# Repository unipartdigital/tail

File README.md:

# Tail
Tail - an indoor position system using UWB radio

# Description

Tail consists of tags, anchors and a server.

A tag is a battery-powered device which occasionally transmits a packet on UWB radio.

An anchor is an externally-powered device in a fixed location which acts as a bridge between UWB radio and the network on which the server resides.

The server sends and receives packets via the anchors, and is able to compute the location of each tag using multilateration.

A simpler mode of operation has also been developed whereby an anchor and a tag perform two-way communications to establish a distance between a tag and a single anchor.

# Status

Tail has been developed to a functional demo in a constrained test environment. It requires further development before it can be used in a production environment.

Unipart Digital is not currently developing this project past this stage.

# Video

Unipart Digital produced a video showing how the system works, and demonstrating it in action. The video is available here:

https://unipart.digital/images/projects/tail/tail-commercial.mp4

# Repositories

## tail
This repository is the monorepo that was used for the duration of the development project, so contains everything related to the tags - firmware, hardware, CAD etc,
various works on the anchor software as well as a number of scripts, utilities and other bits and pieces.

## dw1000
https://github.com/unipartdigital/dw1000

This contains hardware and drivers for a DW1000 interface card for a Raspberry Pi

## utrack-tail
https://github.com/unipartdigital/utrack-tail

This repository contains the standalone anchor code required for the two-way communications mode.

## tail-server
https://github.com/unipartdigital/tail-server

This repository contains the latest attempt at developing a multilaterating server for the one way ranging mode.

## tail-anchor-hardware
https://github.com/unipartdigital/tail-anchor-hardware

This repository contains the hardware for a standalone anchor

## tail-anchor-firmware
https://github.com/unipartdigital/tail-anchor-firmware

This repository contains the (as yet barely started) firmware for a standalone anchor

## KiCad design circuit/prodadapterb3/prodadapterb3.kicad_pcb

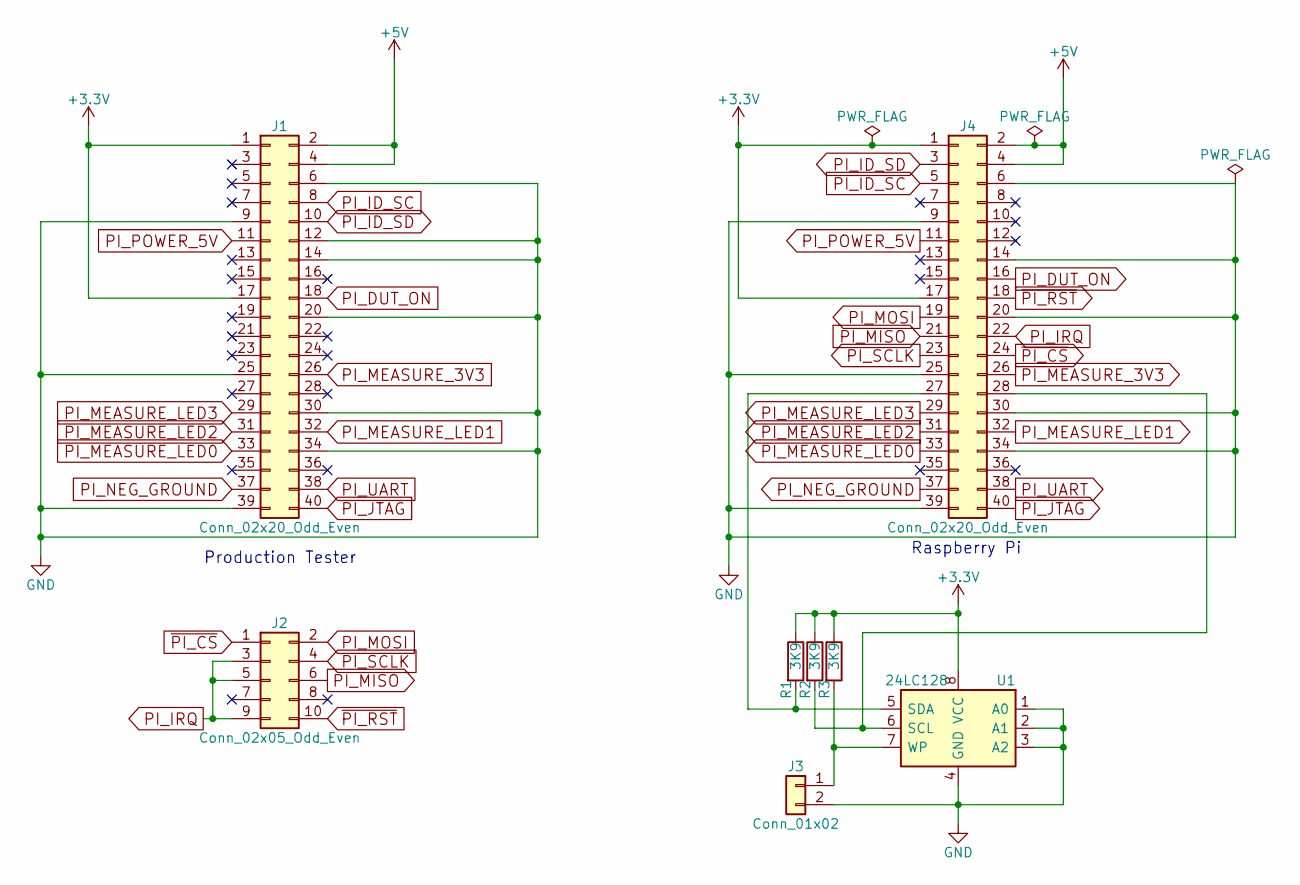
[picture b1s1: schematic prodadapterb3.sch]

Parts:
J1, J4: Conn_02x20_Odd_Even; Pin_Header_Angled_2x20_Pitch2.54mm; MPN 09 18 540 6903
J2: Conn_02x05_Odd_Even; Pin_Header_Angled_2x05_Pitch1.27mm; MPN FTSH-105-01-L-D-RA-K
J3: Conn_01x02; Pin_Header_Straight_1x02_Pitch2.54mm; MPN 2211S-02G
R1, R2, R3: 3K9; R_Axial_DIN0204_L3.6mm_D1.6mm_P5.08mm_Horizontal; MPN MF12 3K9
U1: 24LC128; DIP-8_W7.62mm; MPN 24LC128-I/P

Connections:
+3V3: J1.1, J1.17, J4.1, J4.17, R1.1, R2.1, R3.1, U1.8 (VCC)
+5V: J1.2, J1.4, J4.2, J4.4
GND: J1.6, J1.9, J1.12, J1.14, J1.20, J1.25, J1.30, J1.34, J1.39, J3.2, J4.6, J4.9, J4.14, J4.20, J4.25, J4.30, J4.34, J4.39, U1.1 (A0), U1.2 (A1), U1.3 (A2), U1.4 (GND)
unnamed: J3.1, R3.2, U1.7 (WP)
unnamed: J4.27, R1.2, U1.5 (SDA)
unnamed: J4.28, R2.2, U1.6 (SCL)
PI_DUT_ON: J1.18, J4.16
PI_ID_SC: J1.8, J4.5
PI_ID_SD: J1.10, J4.3
PI_IRQ: J2.3, J2.5, J2.9, J4.22
PI_JTAG: J1.40, J4.40
PI_MEASURE_3V3: J1.26, J4.26
PI_MEASURE_LED0: J1.33, J4.33
PI_MEASURE_LED1: J1.32, J4.32
PI_MEASURE_LED2: J1.31, J4.31
PI_MEASURE_LED3: J1.29, J4.29
PI_MISO: J2.6, J4.21
PI_MOSI: J2.2, J4.19
PI_NEG_GROUND: J1.37, J4.37
PI_POWER_5V: J1.11, J4.11
PI_SCLK: J2.4, J4.23
PI_UART: J1.38, J4.38
~PI_CS: J2.1, J4.24
~PI_RST: J2.10, J4.18

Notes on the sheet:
Raspberry Pi
Production Tester

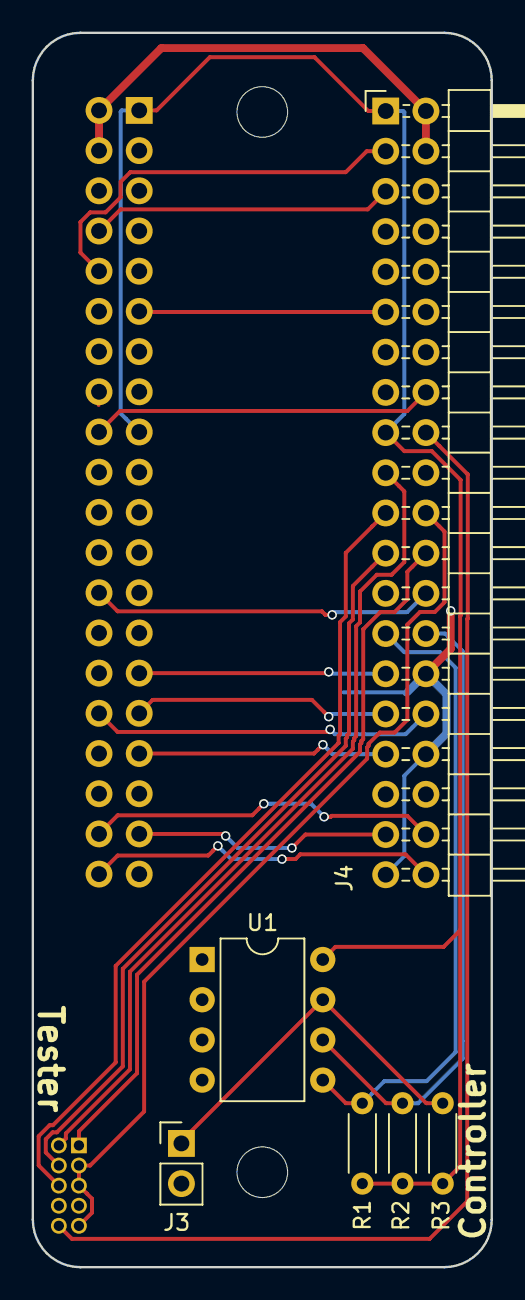
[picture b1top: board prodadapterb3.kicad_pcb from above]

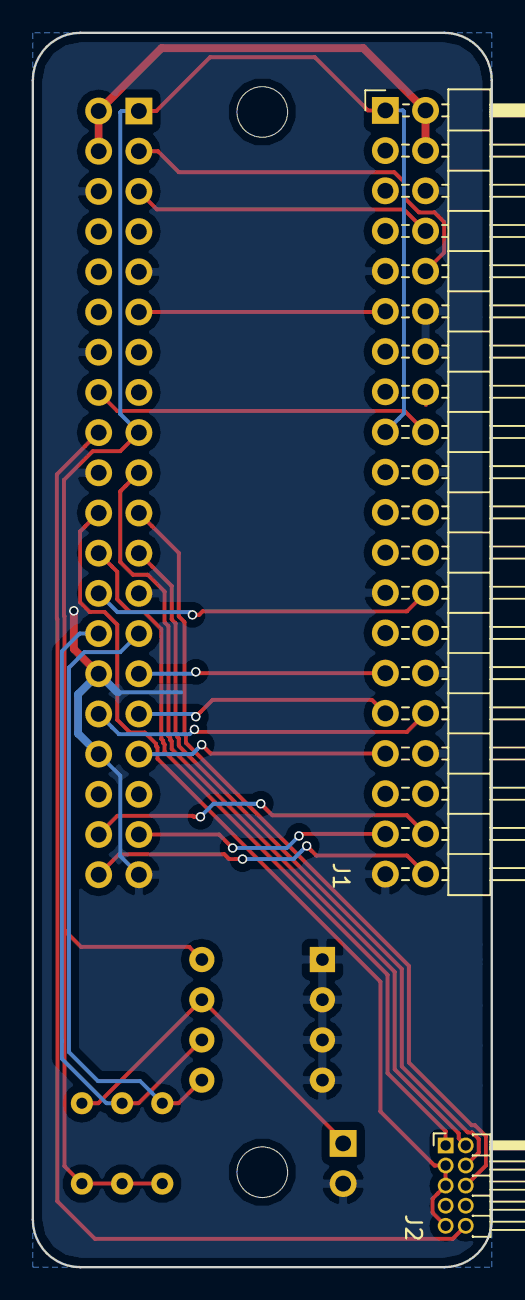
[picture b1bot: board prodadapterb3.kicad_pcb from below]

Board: 2 copper layers, 29.0 x 78.0 mm, 8 parts (2 on the bottom side), 24 nets.

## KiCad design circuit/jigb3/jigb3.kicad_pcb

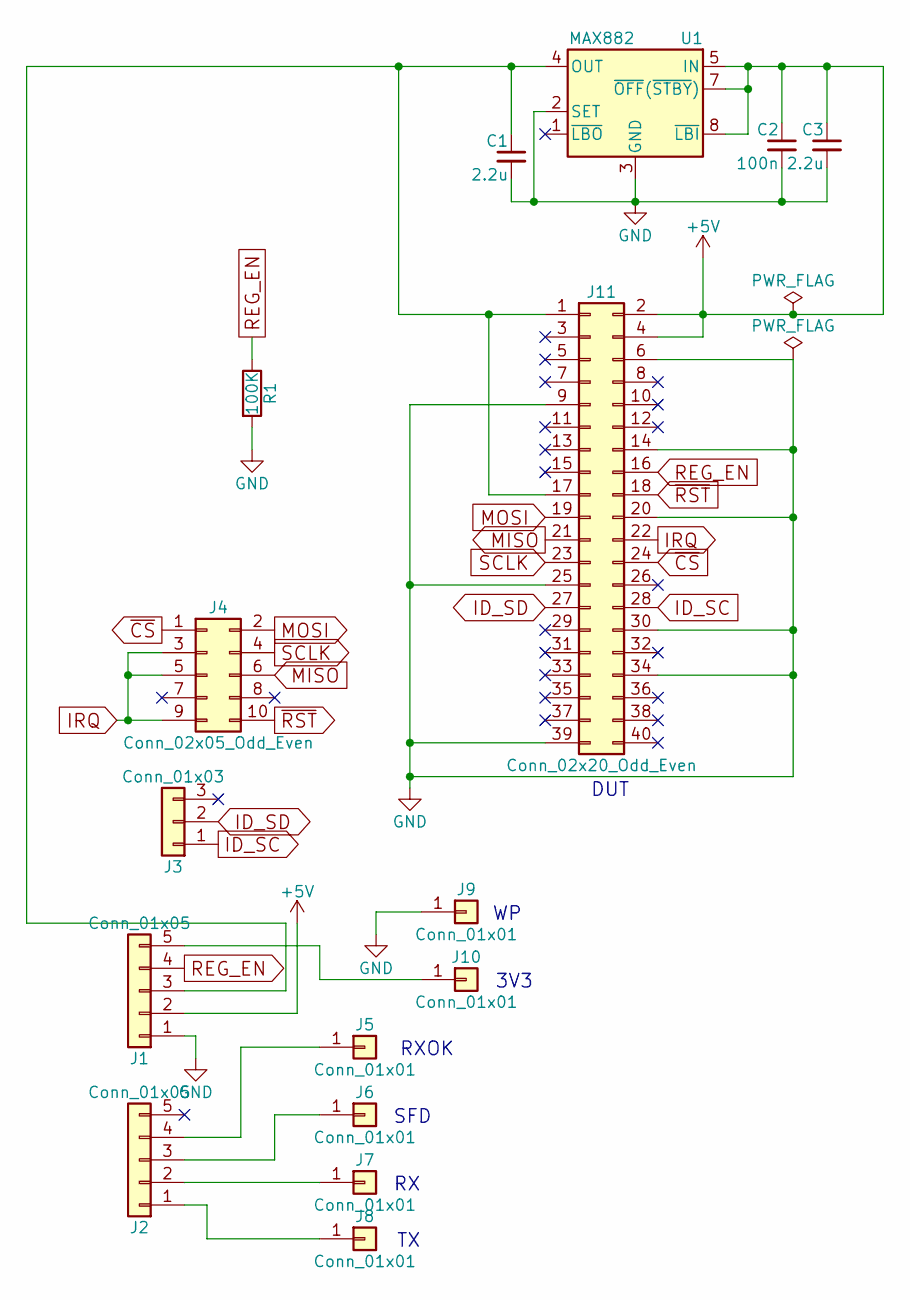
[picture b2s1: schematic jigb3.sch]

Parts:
C1, C3: 2.2u; CP_Radial_D5.0mm_P2.00mm; MPN MCRH100V225M5X11
C2: 100n; C_Disc_D5.0mm_W2.5mm_P5.00mm; MPN K104K15X7RF53H5
J1, J2: Conn_01x05; Pin_Header_Angled_1x05_Pitch2.54mm; MPN 61300511021
J3: Conn_01x03; Pin_Header_Angled_1x03_Pitch2.54mm; MPN 61300311021
J4: Conn_02x05_Odd_Even; Pin_Header_Angled_2x05_Pitch1.27mm; MPN FTSH-105-01-L-D-RA-K
J5, J6, J7, J8, J9, J10: Conn_01x01; P70-2200045; MPN P70-2200045
J11: Conn_02x20_Odd_Even; Pin_Header_Straight_2x20_Pitch2.54mm; MPN 2213S-40G
R1: 100K; R_Axial_DIN0204_L3.6mm_D1.6mm_P5.08mm_Horizontal; MPN MF12 100K
U1: MAX882; DIP-8_W7.62mm; MPN MAX882CPA+

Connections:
+5V: C2.1, C3.1, J1.2, J11.2, J11.4, U1.5 (IN), U1.7 (~OFF~(~STBY~)), U1.8 (~LBI)
GND: C1.2, C2.2, C3.2, J1.1, J9.1, J11.6, J11.9, J11.14, J11.20, J11.25, J11.30, J11.34, J11.39, R1.2, U1.2 (SET), U1.3 (GND), U1.6 (GND)
ID_SC: J3.1, J11.28
ID_SD: J3.2, J11.27
IRQ: J4.3, J4.5, J4.9, J11.22
MISO: J4.6, J11.21
MOSI: J4.2, J11.19
unnamed: C1.1, J1.3, J11.1, J11.17, U1.4 (OUT)
unnamed: J1.5, J10.1
unnamed: J2.1, J8.1
unnamed: J2.2, J7.1
unnamed: J2.3, J6.1
unnamed: J2.4, J5.1
REG_EN: J1.4, J11.16, R1.1
SCLK: J4.4, J11.23
~CS: J4.1, J11.24
~RST: J4.10, J11.18

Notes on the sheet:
DUT
3V3
RXOK
SFD

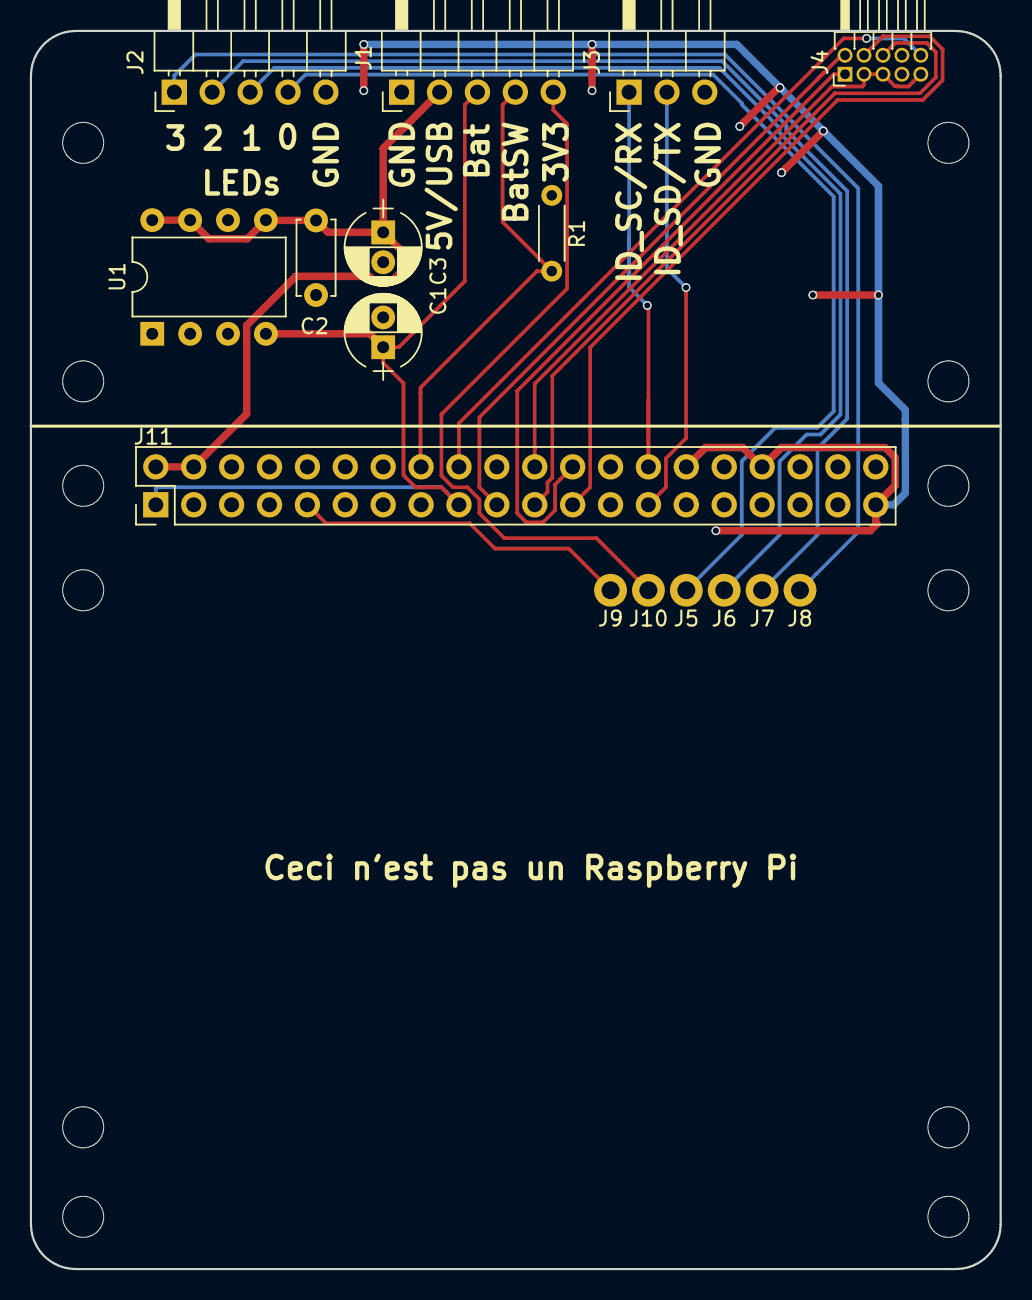
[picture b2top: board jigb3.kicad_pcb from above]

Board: 2 copper layers, 65.0 x 83.0 mm, 16 parts (0 on the bottom side), 17 nets.

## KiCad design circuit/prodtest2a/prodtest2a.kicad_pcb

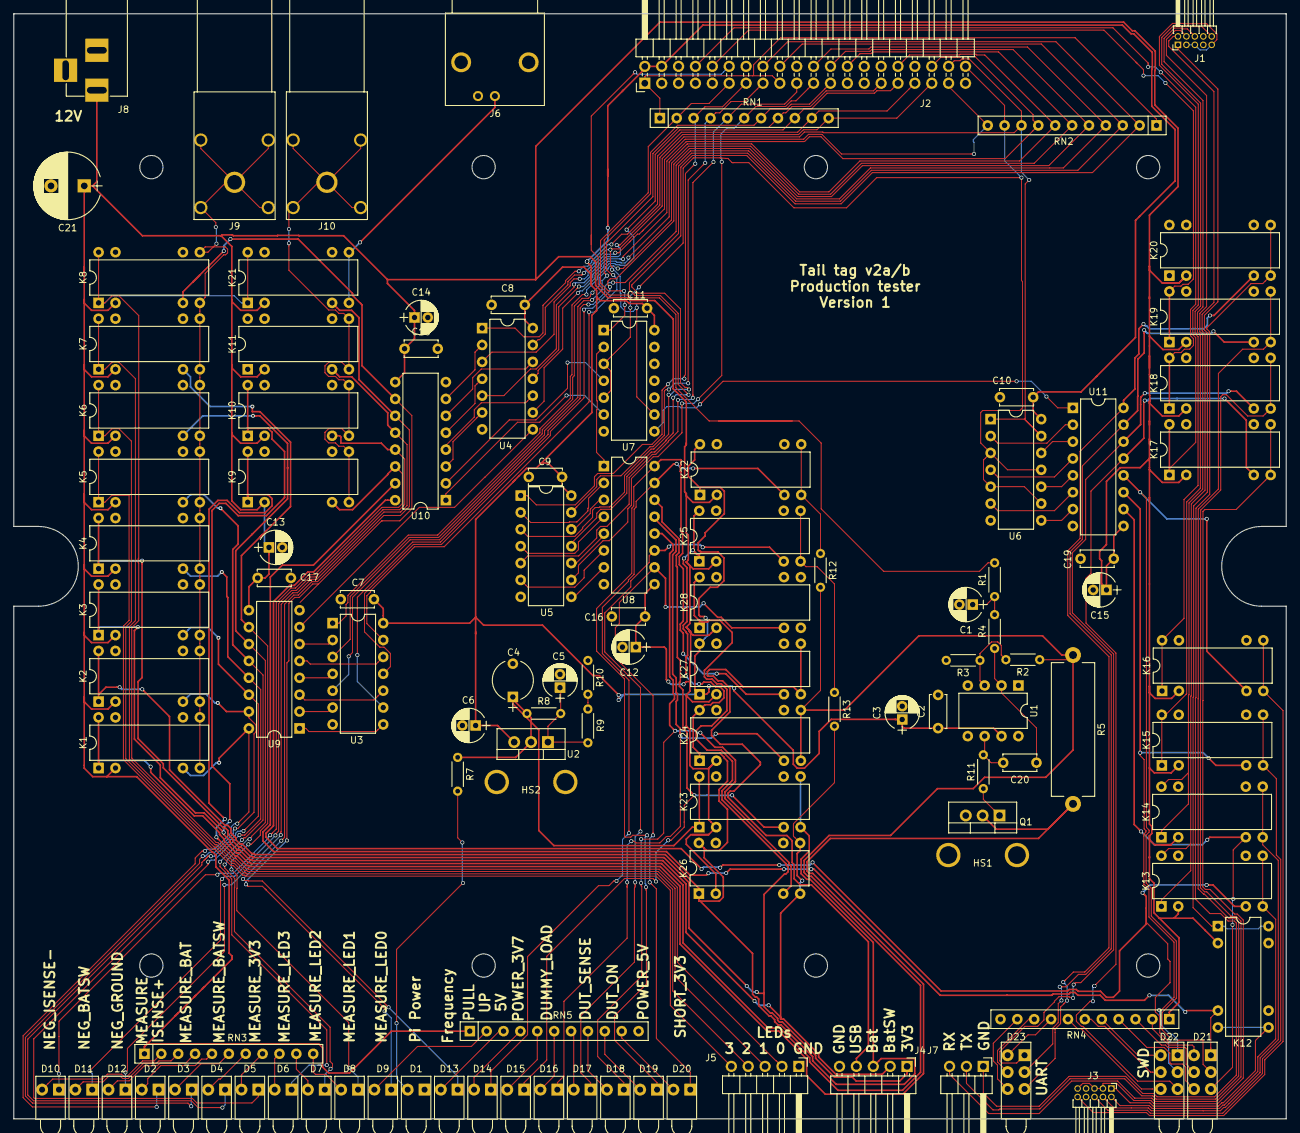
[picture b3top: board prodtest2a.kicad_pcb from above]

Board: 2 copper layers, 191.5 x 166.3 mm, 113 parts (0 on the bottom side), 150 nets.

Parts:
C1, C3, C5, C6, C12, C13, C14, C15: 10u; CP_Radial_D5.0mm_P2.00mm
C2, C7, C8, C9, C10, C11, C16, C17, C18, C19, C20: 100n; C_Disc_D5.0mm_W2.5mm_P5.00mm
C4: 22u; CP_Radial_Tantal_D6.0mm_P5.00mm
C21: 1000u; CP_Radial_D10.0mm_P5.00mm
D1: GREEN; LED_D3.0mm_Horizontal_Housing_Z5.0mm
D2, D3, D4, D5, D6, D7, D8, D9, D10, D11, D12, D13, D14, D15, D16, D17, D18, D19, D20: RED; LED_D3.0mm_Horizontal_Housing_Z5.0mm
D21, D22, D23: Green; LED_D3.0mm_Horizontal_Housing_Triple
HS1, HS2: Heatsink; Heatsink_Aavid_581002B02500G
J1, J3: Conn_02x05_Odd_Even; Pin_Header_Angled_2x05_Pitch1.27mm
J2: Conn_02x20_Odd_Even; Pin_Header_Angled_2x20_Pitch2.54mm
J4, J5: Conn_01x05; Pin_Header_Angled_1x05_Pitch2.54mm
J6: Conn_Coaxial; BNC_Elbow_Socket_TE_1-1337543-0
J7: Conn_01x03; Pin_Header_Angled_1x03_Pitch2.54mm
J8: Barrel_Jack; BARREL_JACK
J9: Banana Red; Staubli_4mm_Angled_Socket
J10: Banana Black; Staubli_4mm_Angled_Socket
K1, K2, K3, K4, K5, K6, K7, K8, K9, K10, K11, K12, K13, K14, K15, K16, K17, K18, K19, K20, K21, K22, K23, K24, K25, K26, K27, K28: HE721A; DIP-14_8_W7.62mm
Q1: IPP034N03L; TO-220-3_Vertical
R1: 4k7; R_Axial_DIN0204_L3.6mm_D1.6mm_P5.08mm_Horizontal
R2, R3: 100k; R_Axial_DIN0204_L3.6mm_D1.6mm_P5.08mm_Horizontal
R4, R13: 10k; R_Axial_DIN0204_L3.6mm_D1.6mm_P5.08mm_Horizontal
R5: 0R2; R_Axial_Power_L20.0mm_W6.4mm_P22.40mm
R7, R8, R9, R10: 100; R_Axial_DIN0204_L3.6mm_D1.6mm_P5.08mm_Horizontal
R11, R12: 1k; R_Axial_DIN0204_L3.6mm_D1.6mm_P5.08mm_Horizontal
RN1, RN2: 10k; R_Array_SIP11
RN3, RN4, RN5: 1k; R_Array_SIP11
U1: MCP601-xP; DIP-8_W7.62mm
U2: LM1084-ADJ; TO-220-3_Vertical
U3, U4, U5, U6, U7: 74HCT04; DIP-14_W7.62mm
U8, U9, U10, U11: ULN2003A; DIP-16_W7.62mm

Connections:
3V3: J4.1, K4.1, K4.14, K28.1, K28.14
3V7: C4.1, K23.1, K23.14, R7.1, R8.1, U2.2
+5V: C2.1, C3.1, C6.1, C7.1, C8.1, C9.1, C10.1, C11.1, J2.2, J2.4, K22.1, K22.14, K27.1, K27.14, U1.7, U2.3, U3.14, U4.14, U5.14, U6.14, U7.14
+12V: C12.1, C13.1, C14.1, C15.1, C16.1, C17.1, C18.1, C19.1, C21.1, J8.1, K1.2, K2.2, K3.2, K4.2, K5.2, K6.2, K7.2, K8.2, K9.2, K10.2, K11.2, K12.2, K13.2, K14.2, K15.2, K16.2, K17.2, K18.2, K19.2, K20.2, K21.2, K22.2, K23.2, K24.2, K25.2, K26.2, K27.2, K28.2, RN3.1, RN4.1, RN5.1, U8.9, U9.9, U10.9, U11.9
BATSIM: K1.1, K1.14, K24.7, K24.8, R2.1, R5.1, R12.2
Bat: J4.3, K2.1, K2.14, K23.7, K23.8, K24.1, K24.14, K25.1, K25.14, K26.1, K26.14
BatSW: J4.2, K3.1, K3.14, K10.1, K10.14, K26.7, K26.8, R13.2
C_DUMMY_LOAD: D16.1, K24.6, U8.13
C_DUT_ON: D18.1, K26.6, U8.12
C_DUT_SENSE: D17.1, K25.6, U8.11
C_FREQUENCY: D13.1, K21.6, U10.11
C_MEASURE_3V3: D5.1, K4.6, U9.13
C_MEASURE_BAT: D3.1, K2.6, U9.15
C_MEASURE_BATSW: D4.1, K3.6, U9.14
C_MEASURE_ISENSE+: D2.1, K1.6, U9.16
C_MEASURE_LED0: D9.1, K8.6, U10.10
C_MEASURE_LED1: D8.1, K7.6, U9.10
C_MEASURE_LED2: D7.1, K6.6, U9.11
C_MEASURE_LED3: D6.1, K5.6, U9.12
C_NEG_BATSW: D11.1, K10.6, U10.13
C_NEG_GROUND: D12.1, K11.6, U10.12
C_NEG_ISENSE-: D10.1, K9.6, U10.14
C_POWER_3V7: D15.1, K23.6, U8.14
C_POWER_5V: D19.1, K27.6, U8.16
C_PULLUP_5V: D14.1, K22.6, U8.15
C_SHORT_3V3: D20.1, K28.6, U8.10
C_SWCLK: D21.3, K14.6, U11.10
C_SWDIO: D21.2, K13.6, U10.16
C_SWD_GND: D22.3, K17.6, U11.13
C_SWD_RESET: D22.2, K16.6, U11.12
C_SWD_VCC: D21.1, K12.6, U10.15
C_SWO: D22.1, K15.6, U11.11
C_UART_GND: D23.3, K20.6, U11.16
C_UART_RX: D23.1, K18.6, U11.14
C_UART_TX: D23.2, K19.6, U11.15
FREQUENCY: J6.1, K21.7, K21.8
GND: C1.2, C2.2, C3.2, C4.2, C5.2, C6.2, C7.2, C8.2, C9.2, C10.2, C11.2, C12.2, C13.2, C14.2, C15.2, C16.2, C17.2, C18.2, C19.2, C21.2, D1.1, J2.6, J2.9, J2.14, J2.20, J2.25, J2.30, J2.34, J2.39, J4.5, J6.2, J8.2, J8.3, K11.1, K11.14, K20.1, K20.14, K28.7, K28.8, Q1.3, R3.2, R10.2, U1.4, U3.7, U4.7, U5.7, U6.7, U7.7, U7.11, U7.13, U8.8, U9.8, U10.8, U11.8
ISENSE-: K9.1, K9.14, Q1.2, R5.2
LED0: J5.2, K8.1, K8.14, K21.1, K21.14
LED1: J5.3, K7.1, K7.14
LED2: J5.4, K6.1, K6.14
LED3: J5.5, K5.1, K5.14
METER+: J9.1, K1.7, K1.8, K2.7, K2.8, K3.7, K3.8, K4.7, K4.8, K5.7, K5.8, K6.7, K6.8, K7.7, K7.8, K8.7, K8.8
METER-: J10.1, K9.7, K9.8, K10.7, K10.8, K11.7, K11.8
unnamed: C1.1, R1.1, R4.2
unnamed: C5.1, R8.2, R9.1, U2.1
unnamed: C20.1, R4.1, U1.2
unnamed: C20.2, R11.2, U1.6
unnamed: D1.2, R7.2
unnamed: D2.2, RN3.5
unnamed: D3.2, RN3.6
unnamed: D4.2, RN3.7
unnamed: D5.2, RN3.8
unnamed: D6.2, RN3.9
unnamed: D7.2, RN3.10
unnamed: D8.2, RN3.11
unnamed: D9.2, RN5.2
unnamed: D10.2, RN3.2
unnamed: D11.2, RN3.3
unnamed: D12.2, RN3.4
unnamed: D13.2, RN5.3
unnamed: D14.2, RN5.4
unnamed: D15.2, RN5.5
unnamed: D16.2, RN5.6
unnamed: D17.2, RN5.7
unnamed: D18.2, RN5.8
unnamed: D19.2, RN5.9
unnamed: D20.2, RN5.10
unnamed: D21.4, RN4.4
unnamed: D21.5, RN4.3
unnamed: D21.6, RN4.2
unnamed: D22.4, RN4.7
unnamed: D22.5, RN4.6
unnamed: D22.6, RN4.5
unnamed: D23.4, RN4.10
unnamed: D23.5, RN4.9
unnamed: D23.6, RN4.8
unnamed: J2.1, J2.17, RN1.1, RN2.1
unnamed: K22.7, K22.8, R12.1
unnamed: K25.7, K25.8, R13.1
unnamed: Q1.1, R11.1
unnamed: R2.2, R3.1, U1.3
unnamed: R9.2, R10.1
unnamed: U3.2, U9.6
unnamed: U3.4, U9.4
unnamed: U3.6, U9.2
unnamed: U3.8, U9.1
unnamed: U3.10, U9.3
unnamed: U3.12, U9.5
unnamed: U4.8, U9.7
unnamed: U5.2, U8.2
unnamed: U5.4, U8.4
unnamed: U5.6, U8.6
unnamed: U5.8, U8.7
unnamed: U5.10, U8.5
unnamed: U5.12, U8.3
unnamed: U7.2, U8.1
unnamed: U7.6, U10.1
unnamed: U7.4, U10.2
unnamed: U4.6, U10.3
unnamed: U4.10, U10.4
unnamed: U4.4, U10.5
unnamed: U4.12, U10.6
unnamed: U4.2, U10.7
unnamed: U7.8, U11.1
unnamed: U6.2, U11.2
unnamed: U6.12, U11.3
unnamed: U6.4, U11.4
unnamed: U6.10, U11.5
unnamed: U6.6, U11.6
unnamed: U6.8, U11.7
PI_DUMMY_LOAD: J2.16, RN2.2, U5.3
PI_DUT_ON: J2.18, RN2.3, U5.11
PI_DUT_SENSE: J2.19, RN1.5, U5.5
PI_JTAG: J2.40, RN2.10, U6.3, U6.5, U6.9, U6.11, U7.3, U7.5
PI_MEASURE_3V3: J2.26, RN2.6, U3.3
PI_MEASURE_BAT: J2.23, RN1.7, U3.5
PI_MEASURE_BATSW: J2.24, RN2.5, U3.11
PI_MEASURE_ISENSE+: J2.22, RN2.4, U3.9
PI_MEASURE_LED0: J2.33, RN1.10, U4.1
PI_MEASURE_LED1: J2.32, RN2.7, U4.9
PI_MEASURE_LED2: J2.31, RN1.9, U3.1
PI_MEASURE_LED3: J2.29, RN1.8, U3.13
PI_NEG_BATSW: J2.36, RN2.8, U4.11
PI_NEG_GROUND: J2.37, RN2.11, U4.3
PI_NEG_ISENSE-: J2.35, RN1.11, U4.5
PI_POWER_3V7: J2.15, RN1.4, U5.13
PI_POWER_5V: J2.11, RN1.2, U7.1
PI_PULLUP_5V: J2.13, RN1.3, U5.1
PI_RXD: J2.10, K19.1, K19.14
PI_SHORT_3V3: J2.21, RN1.6, U5.9
PI_TXD: J2.8, K18.1, K18.14
PI_UART: J2.38, RN2.9, U4.13, U6.1, U6.13, U7.9
PWM_IN: J2.12, R1.2
SWCLK_IN: J1.4, K14.1, K14.14
SWCLK_OUT: J3.4, K14.7, K14.8
SWDIO_IN: J1.2, K13.1, K13.14
SWDIO_OUT: J3.2, K13.7, K13.8
SWD_GND_IN: J1.3, J1.5, J1.9, K17.1, K17.14
SWD_GND_OUT: J3.3, J3.5, J3.9, K17.7, K17.8
SWD_RESET_IN: J1.10, K16.1, K16.14
SWD_RESET_OUT: J3.10, K16.7, K16.8
SWD_VCC_IN: J1.1, K12.1, K12.14
SWD_VCC_OUT: J3.1, K12.7, K12.8
SWO_IN: J1.6, K15.1, K15.14
SWO_OUT: J3.6, K15.7, K15.8
UART_GND: J7.1, K20.7, K20.8
UART_RX: J7.3, K18.7, K18.8
UART_TX: J7.2, K19.7, K19.8
USB: J4.4, K27.7, K27.8

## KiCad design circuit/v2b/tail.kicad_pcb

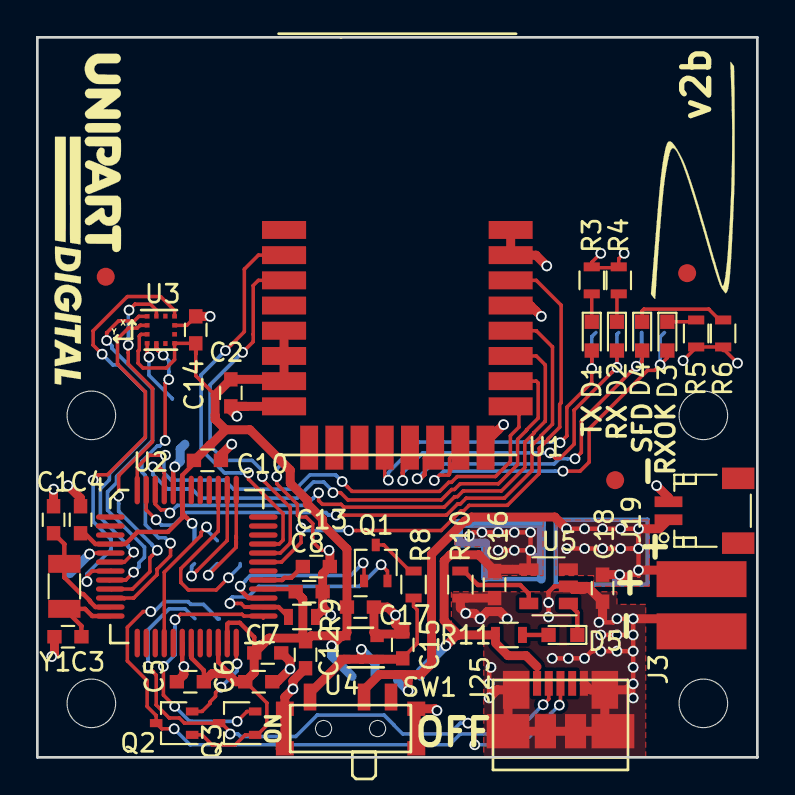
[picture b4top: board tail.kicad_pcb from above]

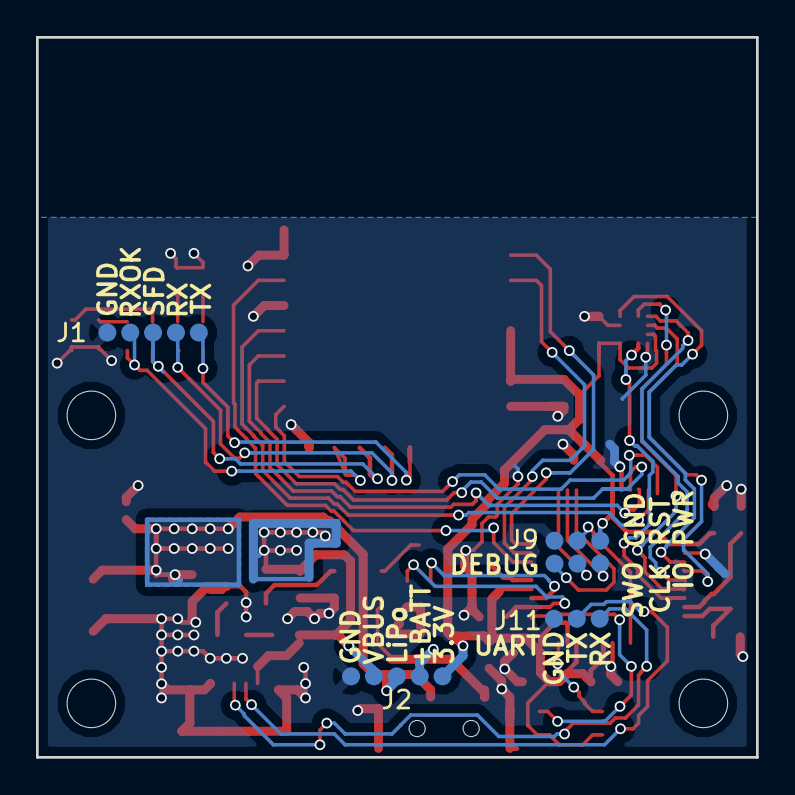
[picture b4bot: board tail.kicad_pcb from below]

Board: 2 copper layers, 40.0 x 40.0 mm, 51 parts (4 on the bottom side), 42 nets.

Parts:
C1, C3: 8p; C_0603
C2, C12: 10u; C_0603
C4, C5, C6, C7, C8, C10, C14, C17: 100n; C_0603
C13, C15: 1u; C_0603
C16, C18: 4.7uF; C_0603
D1, D2, D3, D4, D5: RED; LED_0603
FID1, FID2, FID3: Fiducial; Fiducial_1mm_Dia_2.54mm_Outer_CopperTop
G1: LOGO; Unipart_Digital_logo
G2: LOGO; Tail_logo
J1: LED_DEBUG; LED_DEBUG_Pads
J2: POWER_DEBUG; LED_DEBUG_Pads
J3: LiPo; Battery_SMD
J9: DEBUG; Debug_Pads
J11: UART; UART_Pads
J19: LiPo; JST_SH_SM02B-SRSS-TB_02x1.00mm_Angled
J25: USB_OTG; USB_Micro-B_SMD
Q1, Q2, Q3: Q_NMOS_GSD; SOT-323_SC-70
R3, R4, R5, R6: 150; R_0603
R8, R9: 100K; R_0603
R10: 5.1K; R_0603
R11: 470; R_0603
SW1: SW_SPDT; SWITCH_SSSS811101
U1: DWM1000
U2: EFM32HG222F64; EFM32_TQFP48
U3: MC3630; VLGA-12
U4: XC6215B332NR; SSOT-24
U5: MCP73831-2-OT; SOT-23-5
Y1: 32.768kHz CFPX-217 20ppm 7pF; Crystal_SMD_3215-2pin_3.2x1.5mm

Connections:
+BATT: C15.1, J2.2, R8.1, SW1.1, U4.1, U4.4
ACCEL_CSN: U2.6, U3.10
ACCEL_INTN: U2.10, U3.5
ACCEL_MISO: U2.8, U3.1
ACCEL_MOSI: U2.7, U3.2
ACCEL_PWR: C2.1, C4.1, C5.1, C6.1, C7.1, C8.1, C10.1, C12.1, C14.2, C17.1, J2.1, J9.1, Q2.1, Q3.1, U1.5, U1.6, U1.7, U2.4, U2.19, U2.22, U2.23, U2.28, U2.43, U3.3, U3.7, U4.3
ACCEL_SCK: U2.9, U3.12
BATT_MON: Q1.2, R9.1, U2.26
BATT_MON_EN: Q1.1, U2.27
DBG_RESET: J9.3, U2.16
DBG_SWDCLK: J9.4, U2.37
DBG_SWDIO: J9.2, U2.38
DBG_SWO: J9.6, U2.39
GND: C1.2, C2.2, C3.2, C4.2, C5.2, C6.2, C7.2, C8.2, C10.2, C12.2, C13.2, C14.1, C15.2, C16.2, C17.2, C18.2, J1.1, J2.5, J3.2, J9.5, J11.3, J19.2, J25.5, J25.6, R3.2, R4.2, R5.2, R6.2, R9.2, R10.2, SW1.4, U1.8, U1.16, U1.21, U1.23, U1.24, U2.5, U2.18, U2.44, U3.4, U3.9, U4.2, U5.2
unnamed: C1.1, U2.11, Y1.1
unnamed: C3.1, U2.12, Y1.2
unnamed: C13.1, U2.29
unnamed: C16.1, J2.4, J25.1, R11.1, U5.4
unnamed: C18.1, J2.3, J3.1, J19.1, SW1.2, U5.3
unnamed: D1.1, R3.1
unnamed: D1.2, J1.5, U1.12
unnamed: D2.1, R4.1
unnamed: D2.2, J1.4, U1.13
unnamed: D3.1, R5.1
unnamed: D3.2, J1.2, U1.15
unnamed: D4.1, R6.1
unnamed: D4.2, J1.3, U1.14
unnamed: D5.1, U5.1
unnamed: D5.2, R11.2
unnamed: Q1.3, R8.2
unnamed: R10.1, U5.5
RADIO_CSN: U1.17, U2.48
RADIO_IRQ: U1.22, U2.31
RADIO_MISO: U1.19, U2.46
RADIO_MOSI: U1.18, U2.45
RADIO_RSTN: U1.3, U2.32
RADIO_SCK: U1.20, U2.47
RADIO_WAKEUP: U1.2, U2.33
UART_RX: Q3.2, U2.25
UART_RX_HV: J11.1, J25.3, Q3.3
UART_TX: Q2.2, U2.24
UART_TX_HV: J11.2, J25.2, Q2.3

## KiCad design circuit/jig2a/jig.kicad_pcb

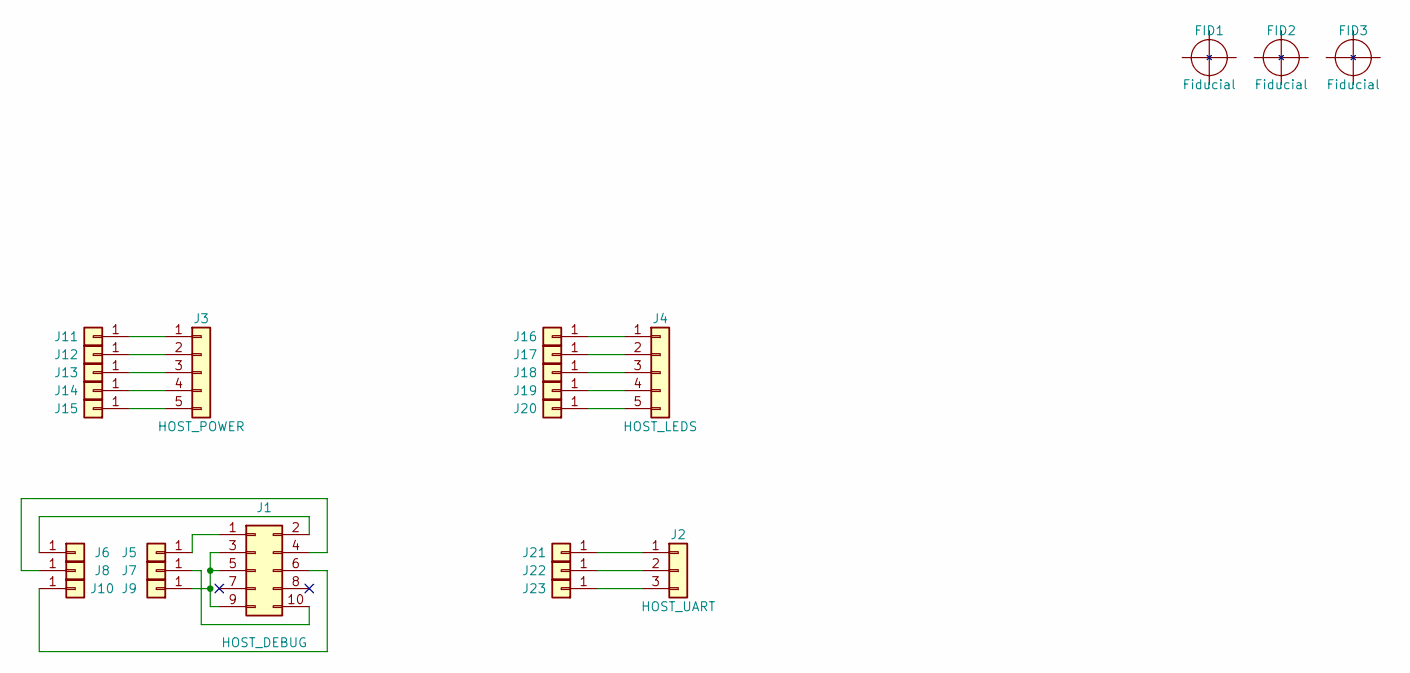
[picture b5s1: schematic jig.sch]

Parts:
FID1, FID2, FID3: Fiducial; Fiducial_1mm_Dia_2.54mm_Outer_CopperTop
J1: HOST_DEBUG; Pin_Header_Straight_2x05_Pitch1.27mm_SMD; MPN FTSH-105-01-L-DV
J2: HOST_UART; Pin_Header_Straight_1x03_Pitch2.54mm; MPN 2211-03G
J3: HOST_POWER; Pin_Header_Straight_1x05_Pitch2.54mm; MPN 2211S-05G
J4: HOST_LEDS; Pin_Header_Straight_1x05_Pitch2.54mm; MPN 2211S-05G
J5, J6, J7, J8, J9, J10, J11, J12, J13, J14, J15, J16, J17, J18, J19, J20, J21, J22, J23: S13; Harwin-Sleeve-S13-1.27mm; MPN S13-503

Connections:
unnamed: J1.1, J5.1
unnamed: J1.2, J6.1
unnamed: J1.3, J1.5, J1.9, J9.1
unnamed: J1.4, J8.1
unnamed: J1.6, J10.1
unnamed: J1.10, J7.1
unnamed: J2.1, J21.1
unnamed: J2.2, J22.1
unnamed: J2.3, J23.1
unnamed: J3.1, J11.1
unnamed: J3.2, J12.1
unnamed: J3.3, J13.1
unnamed: J3.4, J14.1
unnamed: J3.5, J15.1
unnamed: J4.1, J16.1
unnamed: J4.2, J17.1
unnamed: J4.3, J18.1
unnamed: J4.4, J19.1
unnamed: J4.5, J20.1

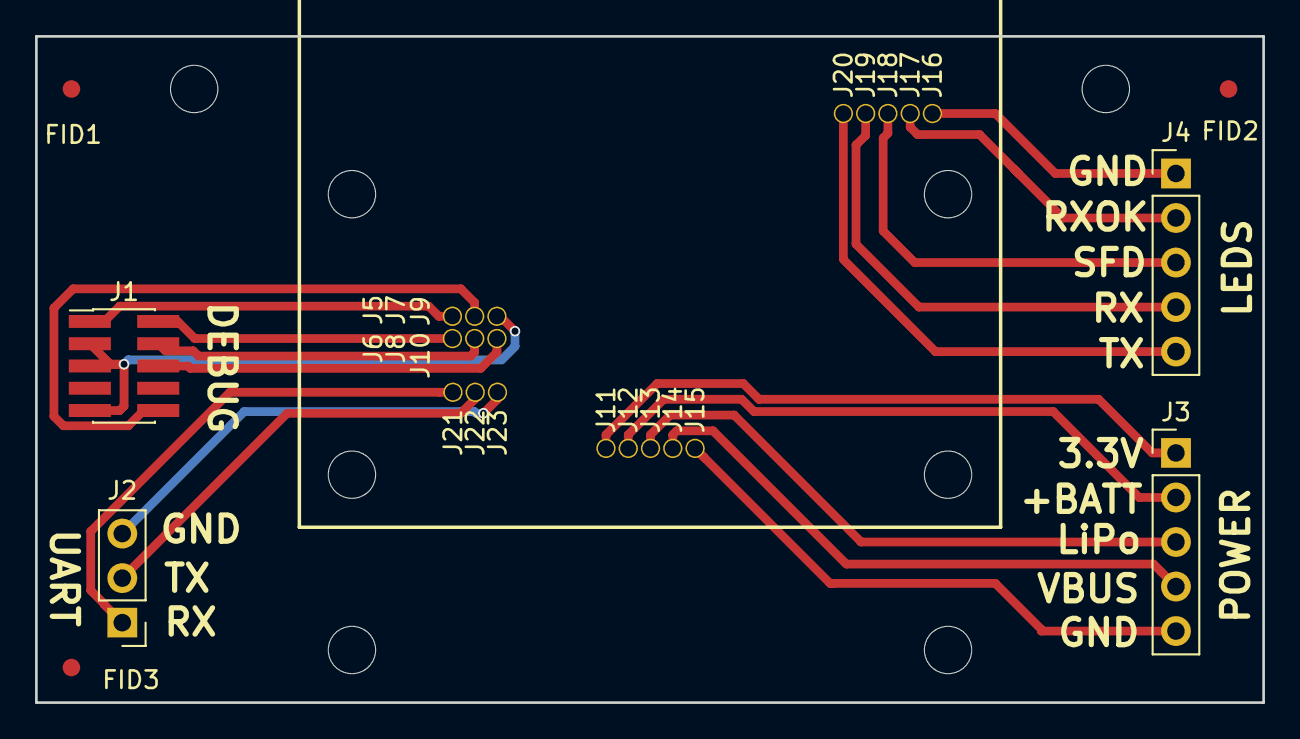
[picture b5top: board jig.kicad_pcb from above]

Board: 2 copper layers, 70.0 x 38.0 mm, 26 parts (0 on the bottom side), 19 nets.

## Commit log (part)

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2018-09-07 firmware: Don't put radio to sleep when transmitting response
2018-09-11 firmware: Allow turnaround delay for ranging to be configured
2018-09-13 WIP loctest.py
2018-09-13 rtls: Make sure anchor service is running with dwcalib.sh
2018-09-17 rtls: Minor improvements in twrtest.py
2018-09-17 rtls: Add peak detection to two-way ranging tools
2018-09-19 WIP plotxy.py
2018-09-20 WIP add loctest algo with ref autoselect
2018-10-01 tail: clone v1 directory into v2
2018-10-02 tail: Add power switch
2018-10-02 tail: minor tweaks
2018-10-02 tail: make a start on board outline and placement
2018-10-04 utrack: Minor betterments
2018-10-04 utrack: Change TestStation to TailStation
2018-10-04 utrack: Pump up the VOLUME
2018-10-09 case: add demo case for tail v2 tag
    The PDF and STL files are for convenience for people who don't have
    FreeCAD installed.
    The svg and dxf files were used to generate the logo on the lid.
2018-10-24 doc: Assign EUI64 numbers for v2 tags
2018-11-05 case: Add optional hole for debug connector
    Controlled by DebugVisible which must be 0 or 1.
2018-11-12 firmware: Implement IPv6 two way ranging
    This also pulls in slightly better support for IPv6 header compression,
    and attempts to very slightly generalise the existing IPv6 code.
    Packets are now filtered before despatch, so that unicast packets intended
    for other devices are ignored.
    This implementation is not optimised, so the turnaround time must be set
    sufficiently high in order to emit responses. Around 5ms is a good start
2018-11-27 rtls: Add RF compensation analysis scripts
2018-11-27 rtls: Improved plotxy.py
2018-11-27 rtls: Add temperature and voltage log handling
2018-11-27 rtls: Add development scripts for RF level compensation
2018-12-03 utrack: Add support to IPv4 to utrack-client (default)
2018-12-08 rtls: Add RF level compensation analysis script
2018-12-10 rtls: Minor cleaning up here and there
2018-12-18 rtls: New calibration procedure
2019-01-15 rtls: Minor improvements all over the place
2019-01-22 rtls: Add TCP connectivity to anchor service
2019-01-28 jig: Create jig PCB for tail v2a PCB
2019-01-28 jig: Add BOM for hardware
2019-01-29 rtls: Add TCP_NODELAY socket option to tail communication
2019-01-29 rtls: calibrate.py working
2019-02-01 rtls: Add Software Timestamp support
2019-02-06 rtls: Add ntpsync.py script
2019-02-06 scripts: Add RPi kernel build scripts
2019-02-08 scripts: Improved RPi make scripts
2019-02-14 jig: Updated details for ordering
2019-02-20 tester: Add tf390 class and periodic polling for the device
    There's framework here for the other devices to be polled
    too, and for the test, when run, to acquire a lock on
    the devices in order to run without interference from
    the poller
2019-02-21 tester: Finish handling of relays, and handle PWM as well
2019-02-21 tester: Provide an effective way of starting the tester
2019-02-28 tester: Fix syntax errors in wrapper script, and start pigpiod.
2019-03-04 scripts: Improvements to build scripts
2019-03-11 firmware: Make IPv6 optional with a view to removing it.
    IPv6 is a lot more complicated than what we need, and is
    not buying us anything. We can cut out considerable code
    and processing time by simply not using IPv6 headers,
    especially since we're not really supporting most of IPv6
    anyway.
2019-03-13 utrack: renamed to lamp
2019-03-22 firmware: Remove some more IPv6 code
2019-03-22 firmware: Remove concept of role. Always start tag functionality
    ... unless EUI is not configured, of course.
2019-03-22 firmware: Move tag command to a more logical place in the list
2019-03-23 firmware: synchronise the host and radio buffers
2019-04-03 firmware: add state register to list of registers to dump
2019-04-07 efm32-base: added as a submodule (for firmware)
2019-04-10 rtls: Minor improvements
2019-04-17 tester: Help libusb find the JTAG interface
2019-04-24 tester: add shutdown button
2019-04-24 firmware: remove debug printing battery voltage
2019-04-25 firmware: Turn on flat battery protection
    Flat battery protection can be disabled by setting allow_flat_battery
    to 1 in the config.
2019-04-25 cleaning 1
2019-04-25 Tests build on arm
2019-05-03 firmware: fix stack corruption bug when flashing partial words
    If data is flashed which is more than a word and not a whole
    multiple of the word size, the stack could be corrupted.
2019-05-03 circuit: Add UART-USB level shifting and reduce charge current
    We need to connect the UART to the USB data pins. As these will present
    5 volts, we need to add level shifting to protect the 3.3 volt mcu.
    We will need to enable the internal pullup on the UART Rx line.
    The host cable we are proposing to use already has a pullup on its
    Rx line.
    While we're here, reduce the charge current to just under 200mA in
2019-05-09 WIP: monolithic renamed tail builds
2019-05-10 defined __ramfunc
2019-05-10 Remove some debug-only IAR-centric files
2019-05-10 it builds
2019-05-14 builds
2019-05-14 removed more code, builds
2019-05-14 still works
2019-05-20 bootloader: Various shenanigans to shrink the bootloader into 2k
2019-05-20 bootloader: add missing file
2019-05-22 bootloader: fix line endings
2019-05-22 bootloader: remove debug in Makefile
2019-05-22 bootloader: Turn off the LFXO before booting
    Just in case we boot something that's not the current tail
    firmware, that is.
2019-05-22 bootloader: Pull up UART rx line
2019-05-28 doc: Allocate EUI64s for v2a tags
2019-05-28 tester: Implement tests
2019-05-28 tester: Show correct ppm on completion of xtal trim
2019-06-04 wip works
2019-06-04 added header
2019-06-06 case: Fix screw hole diameter
    The screw holes were using ScrewRadius instead of ScrewHoleRadius.
2019-06-07 tester: Add EUI64 label printer script
2019-06-11 rtls: Reorganise files in calib/ and rtls/
    Relocate files in rtls/ based on the functionality.
    Create calib/ directory for hat calibration routines.
2019-06-13 config: Cut out first half of rx window
    Now that we've implemented rxdelay, we can remove the first half of
    the rx window and leave the second half intact.
2019-06-13 firmware: Listen periodically if listen_period is set
    A new config key, listen_period, sets the number of seconds
    after which, if a receive window has not been opened, the tag
    will listen even if there is no other reason to. This ensures
    that it is possible to reconfigure a tag with OTA config if
    it is configured to do one way ranging only.
    Note that if the key is not present, a receive window will
2019-06-14 firmware: add xtal_ppm config key
    This key is to be used to enable temperature compensation
    for the xtal trim. For now, it's just a value that the production
    tester will store, but it can be used later by a compensation
    algorithm.
2019-06-14 wip new needing
2019-06-14 Firmware: added filename comment
2019-06-17 tester: Spell Firmware correctly
2019-06-17 config: add jitter
2019-07-04 prodtest2a: Mark voltage of power input
2019-07-04 ci: Add basic Dockerfile for build-testing the firmware
2019-07-09 Test alternative approach
2019-07-24 Moved subtraction to proto
    Also switched to using 32 bit integers to represent entropy and related time.
2019-07-25 firmware: Apply the tail version to the bootloader too
2019-07-25 firmware: Don't report battery information if it is stale
2019-07-25 Space
2019-08-05 config: Switch to a legal radio channel
2019-08-10 ci: Publish built firmware binaries for tagged releases
2019-08-22 uwbdump: Add verbose command line option
2019-08-28 scripts: Update bss control scripts
2019-09-16 rftool: updated
2019-09-16 uwbdump: Improvements
2019-09-17 b3: Plastics for B3 jig
2019-09-25 tester: Change voltage thresholds for manufactured tester h/w
2019-10-02 config: add EUIs to the demo room anchors config
2019-10-09 WIP - UI stub
2019-10-10 WIP - avoid red/green
2019-10-14 demo: Further lateration improvements
2019-10-15 web: Fix tag list view
2019-10-16 web: Use floorplan SVG as definitive source of coordinate system
2019-10-18 web: Rescale floorplan to use metres as user units
    Use metres as user units and millimetres as Inkscape display units
    (since Inkscape has no option to use metres as display units).
2019-10-21 demo: New lateration algorithms
2019-10-30 tester: Add devicetree overlays and ID EEPROM for production tester
    Create a devicetree fragment to be placed in the ID EEPROM of the
    production tester adapter, and a second devicetree fragment to be
    loaded and unloaded dynamically at runtime under control of the
    production tester software.
2019-11-05 prodadapterb3: Move tester connectors to avoid cable twisting
    In order to provide a more straight through approach, the tester
    side connectors are placed on the back of the PCB. This allows the
    cables to be connected without any twisting, as well as simplifying
    the PCB routing.
2019-11-08 python: Move common python files to python/
2019-11-09 eeprom: CE1 pin is an input, not driven high
    It appears that setting the CE1 pin to disabled is not
    sufficient to disable it - the pin is still set to
    something other than the default state (input), presumably
    alternate function for the SPI function.
    So let's explicitly set the pin back to an input.
2019-11-13 python: Shared library improvements
2019-11-18 tester: refactor and add preliminary support for hats
    Support now exists for hats and tags (wip for now).
    The code to read and write the hat eeprom doesn't yet
    exist and the tag side of the refactor isn't yet tested,
    but rudimentary hat testing now seems to work.
2019-11-21 python: More betterments
2019-11-26 calib: Use common anchord with demo
2019-11-28 tester: Fix refactoring bugs introduced in tag testing
2019-12-09 python: New RF function
2019-12-09 web: Create stub "make install" target
2019-12-10 calib: Remove reference anchor grouping
2019-12-16 tester: Fixes to device tree on adapter
2019-12-16 tested: Add default values to hat-eeprom.dts
2019-12-16 tester: Remove hat-eeprom files which are now in config
2020-03-04 demo: Add config-extended.json, with info for anchors 11-15
    This should be identical to config.json, except that it should also
    contain the extra info for anchors 11-15.
2020-03-09 web: Change y translation to make the dot appear in the right place
    I don't know where the previous value came from, but the dot is
    appearing some way off from where other clients are displaying it.
    The new value is found empirically.
2020-03-10 demo: Add timestamp and IEs to lateration output
